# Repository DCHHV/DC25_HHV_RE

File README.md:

# DC25 HHV Reverse Engineering Challenge

## Info
DC25 Hardware Hacking Village Reverse Engineering Challenge

This repo contains all of the sources, eagle files, and gerbers for the DEF CON 25 Hardware Hacking Village Reverse Engineering Challenge.

Do not go any further than this if you do not wish to see spoilers.  The eagle/ folder has all of the PCB files in it, the gerbers or .brd file can be sent off to a fab house to create a PCB if you wish to re-create the challenge yourself.  The .hex file in the top folder is the binary blob that can be programmed in to the microcontroller.

Writeup available in docs/writeup.txt

BOM available in eagle/DC25_HHV_RE-A-BOM.txt

## Instructions

Once you have a kit in-hand, (if you don't yet, go to the HHV and pick one up!) there are two steps to be aware of for this challenge.

The first challenge, is to reverse engineer the schematic of the device itself.  Grab a piece of paper, draw up the schematic, and take it to the HHV.  A correct schematic will earn you a small prize (while available).

The meat of the challenge is the function of the device.  It's locked, find the passcode to unlock it; when unlocked the green LED will remain solid.  There are multiple ways to accomplish this task.  If you are stuck or just not sure how to proceed, come on down to the HHV and ask for help.  Once the device has been unlocked, make your way back to the HHV again to collect a larger prize (while available).

This challenge is meant to be fun for all levels of experience, but is designed to be an introduction to reverse engineering and a demonstration in how insecure some devices really are.

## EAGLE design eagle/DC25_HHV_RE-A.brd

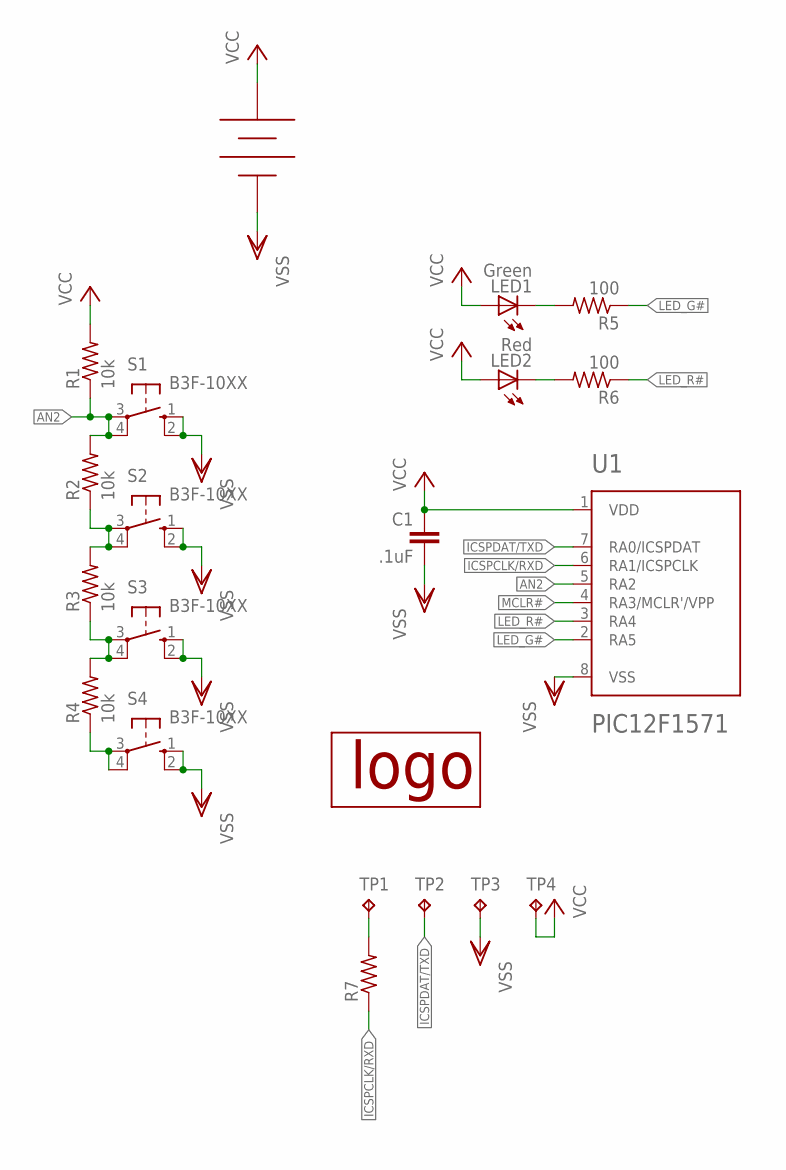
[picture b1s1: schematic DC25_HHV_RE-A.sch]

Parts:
BT1: BAT-HLD-001-THM
C1: .1uF; C050-024X044
LED1: Green; LED5MM
LED2: Red; LED5MM
R1, R2, R3, R4: 10k; 0207/10
R5, R6: 100; 0207/10
R7: R-US_R0402; R0402
S1, S2, S3, S4: B3F-10XX
TP1, TP2, TP3, TP4: TPTP13R; TP13R
U1: PIC12F1571; DIL8
U$1: KBELOGO-SILK

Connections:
AN2: R1.1, R2.2, S1.3, S1.4 (P1), U1.5 (RA2)
ICSPCLK/RXD: R7.1, U1.6 (RA1/ICSPCLK)
ICSPDAT/TXD: TP2.TP, U1.7 (RA0/ICSPDAT)
LED_G#: R5.1, U1.2 (RA5)
LED_R#: R6.1, U1.3 (RA4)
MCLR#: U1.4 (RA3/MCLR'/VPP)
unnamed: R4.1, S4.3, S4.4 (P1)
unnamed: R3.1, R4.2, S3.3, S3.4 (P1)
unnamed: LED2.K (C), R6.2
unnamed: R7.2, TP1.TP
unnamed: R2.1, R3.2, S2.3, S2.4 (P1)
unnamed: LED1.K (C), R5.2
VCC: BT1.+@0 (VCC), BT1.+@1 (VCC), BT1.+@2 (VCC), BT1.+@3 (VCC), C1.1, LED1.A, LED2.A, R1.2, TP4.TP, U1.1 (VDD)
VSS: BT1.- (VSS), C1.2, S1.1 (S), S1.2 (S1), S2.1 (S), S2.2 (S1), S3.1 (S), S3.2 (S1), S4.1 (S), S4.2 (S1), TP3.TP, U1.8 (VSS)

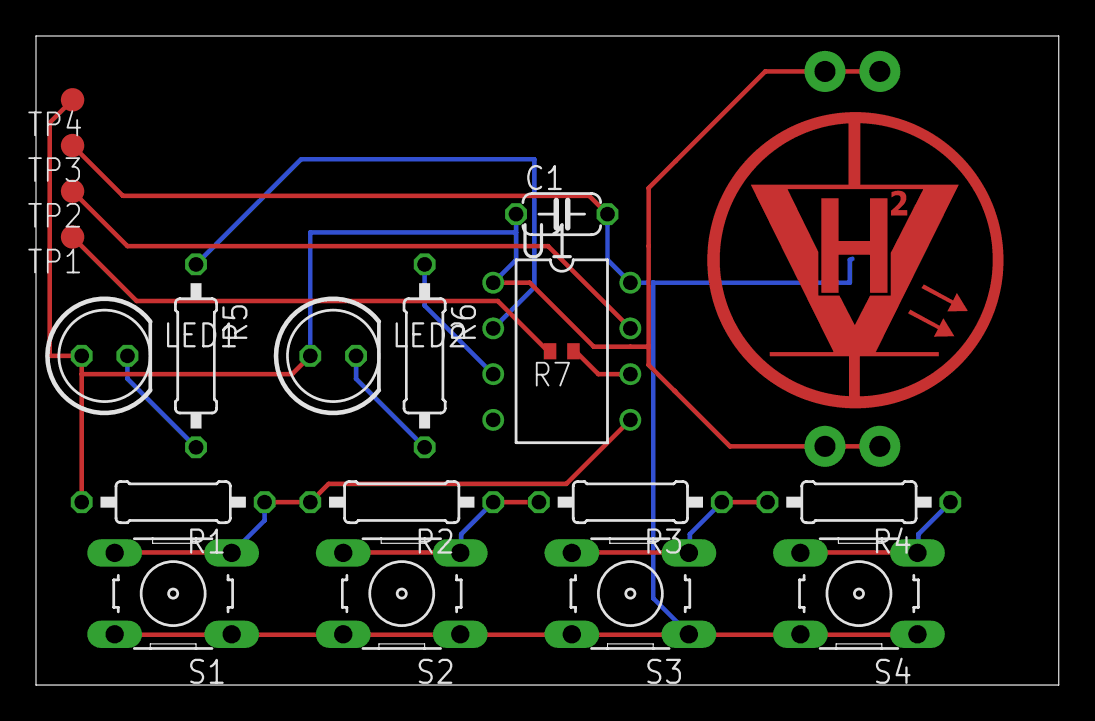
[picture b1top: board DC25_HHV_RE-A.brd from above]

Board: 2 copper layers, 56.8 x 36.1 mm, 21 parts (1 on the bottom side), 13 nets.

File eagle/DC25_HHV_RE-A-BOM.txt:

Partlist exported from /home/karl/my_codes/DC25_HHV_RE/eagle/DC25_HHV_RE-A.sch at 28 Aug 2017 13:11:10

Qty Value           Device          Package         Parts              Description                
1   .1uF            C-EU050-024X044 C050-024X044    C1                 CAPACITOR, European symbol 
2   100             R-US_0207/10    0207/10         R5, R6             RESISTOR, American symbol  
4   10k             R-US_0207/10    0207/10         R1, R2, R3, R4     RESISTOR, American symbol  
4   B3F-10XX        10-XX           B3F-10XX        S1, S2, S3, S4     OMRON SWITCH               
1   BAT-HLD-001-THM BAT-HLD-001-THM BAT-HLD-001-THM BT1                                           
1   PIC12F1571      PIC12F1571      DIL8            U1                 PIC12F1571/2               
1   Green           LED5MM          LED5MM          LED1               LED                        
1   Red             LED5MM          LED5MM          LED2               LED

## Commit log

2017-05-18 Added README.md
2017-07-24 Updated README with temporary information
2017-07-24 Added contest instructions
2017-08-27 Addition of Eagle files Addition of Microchip files
2017-08-27 Added bits to readme file
2017-08-28 Added writeup for the challenge
2017-08-28 Added BOM
2018-04-10 Fixed bug where "unlockit" and "lockit" commands would set the locked flag, but not change the LED state for feedback
